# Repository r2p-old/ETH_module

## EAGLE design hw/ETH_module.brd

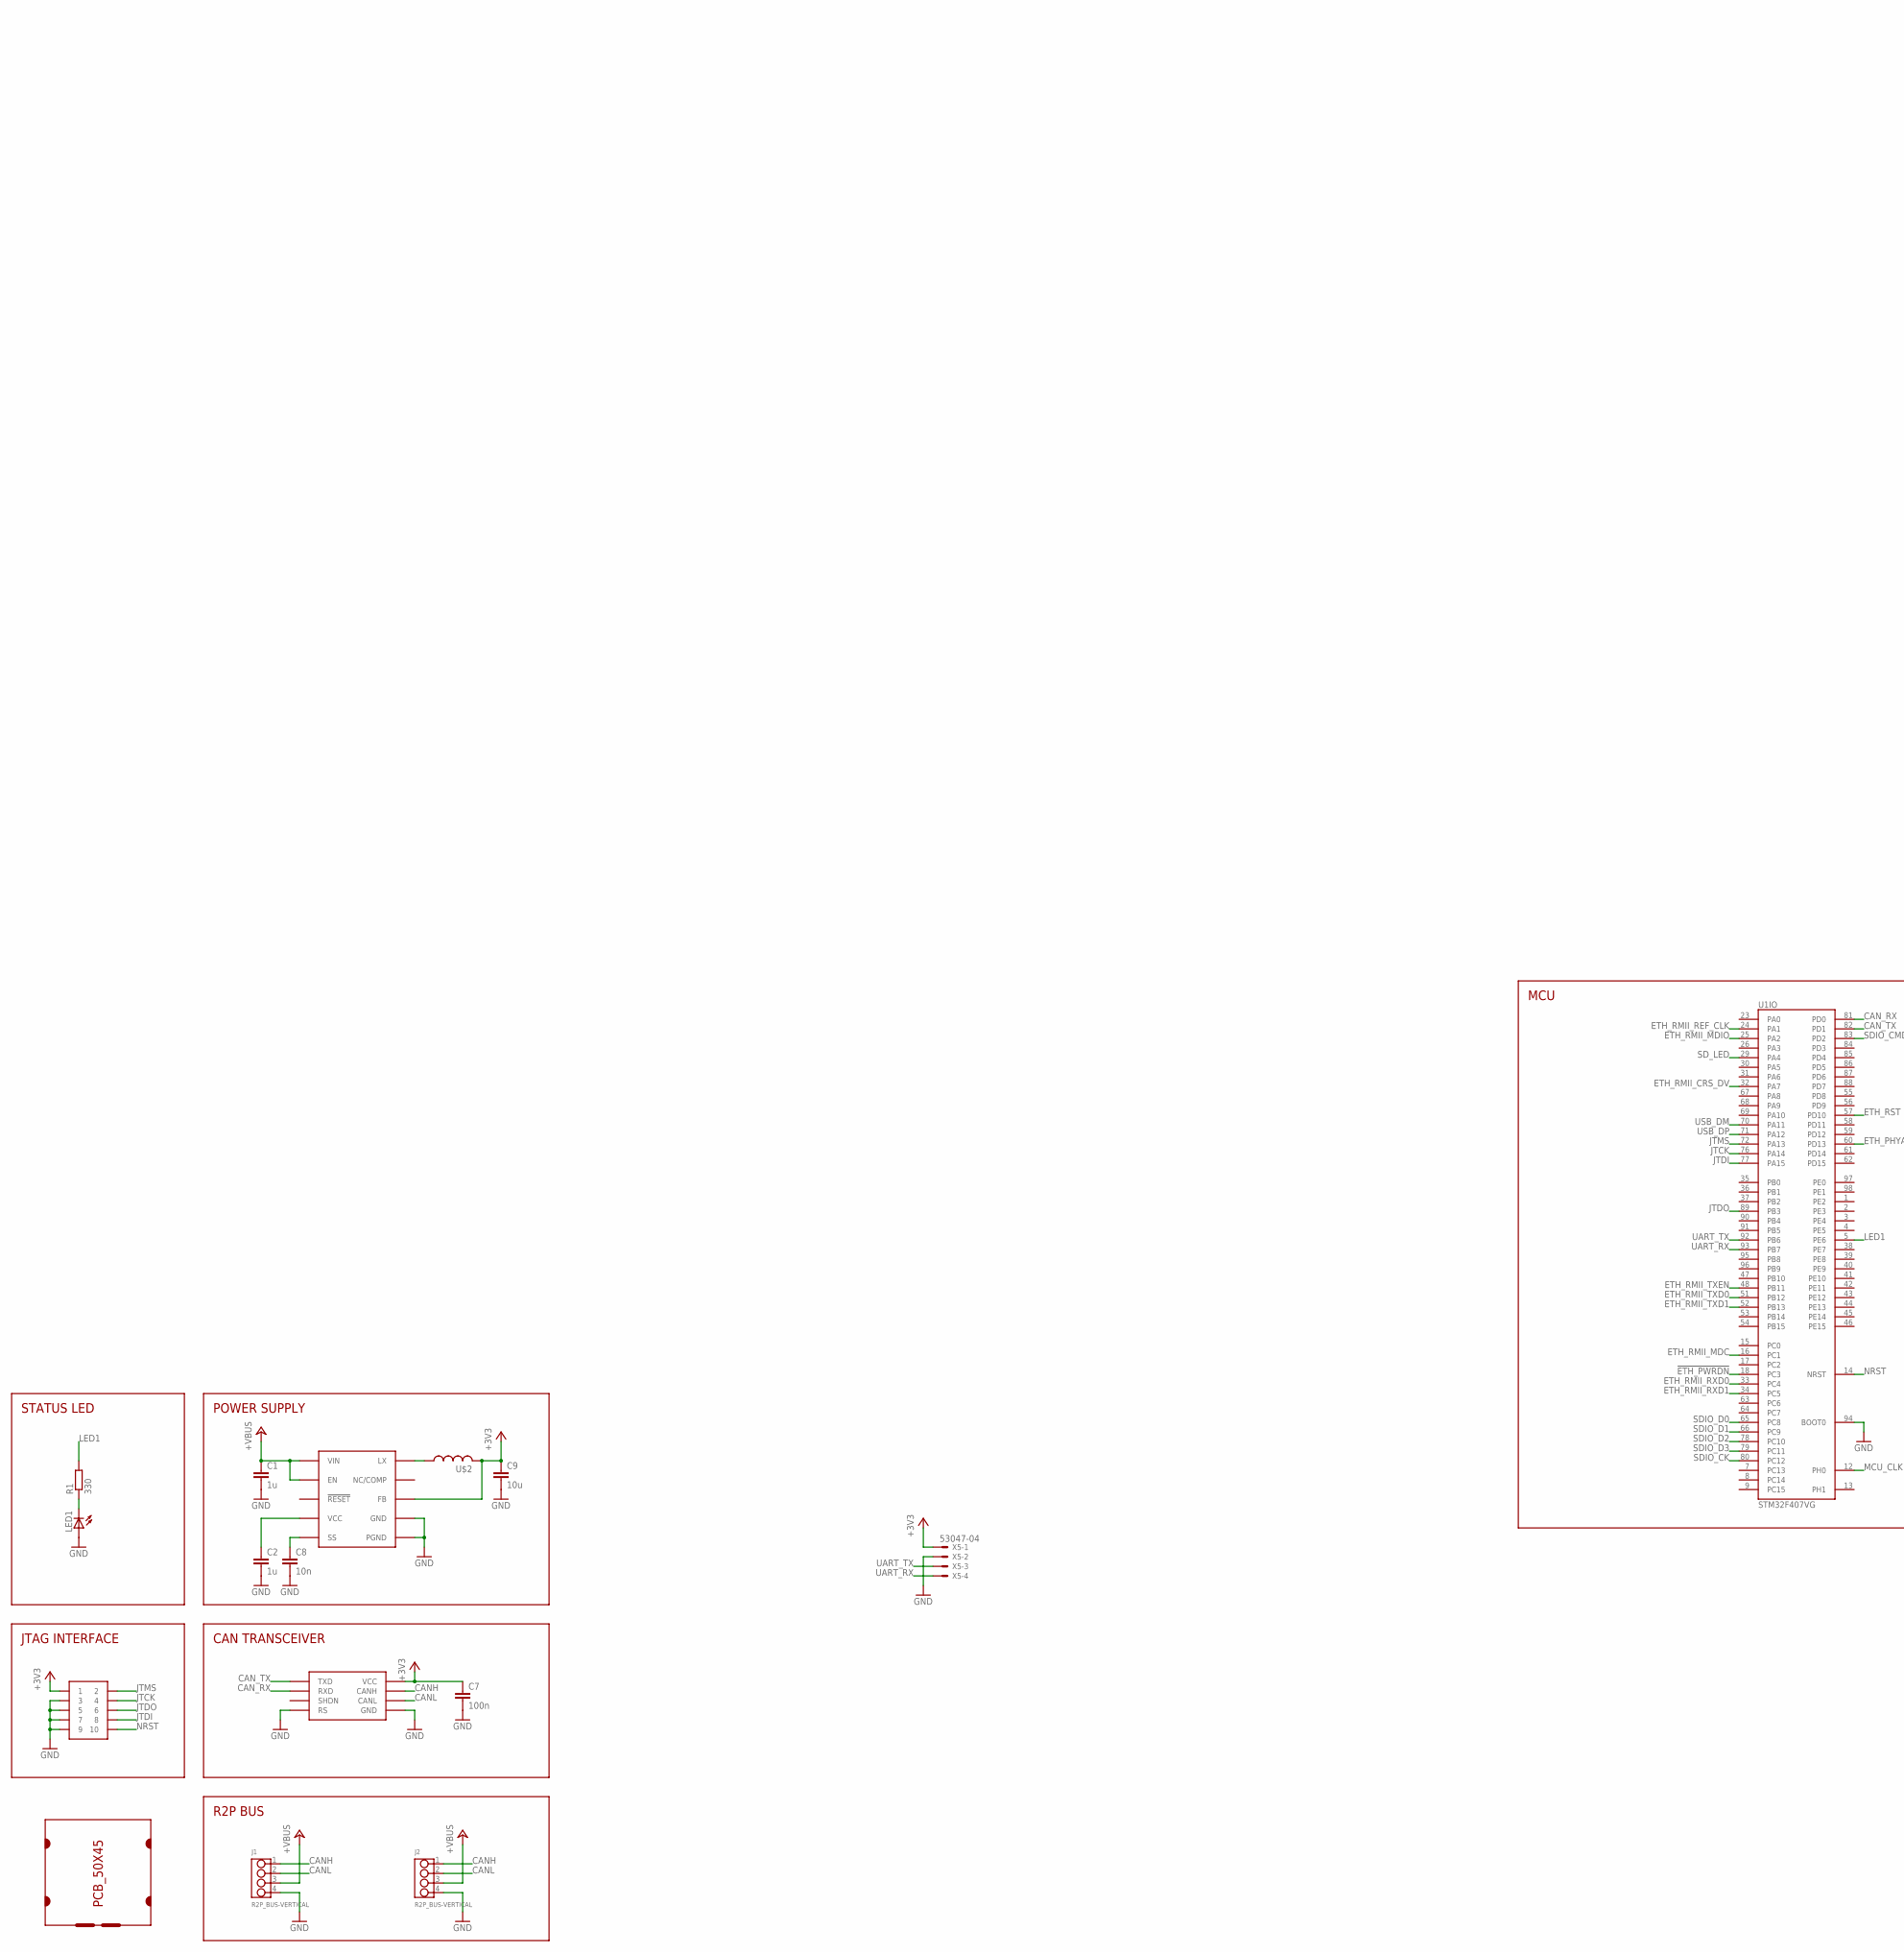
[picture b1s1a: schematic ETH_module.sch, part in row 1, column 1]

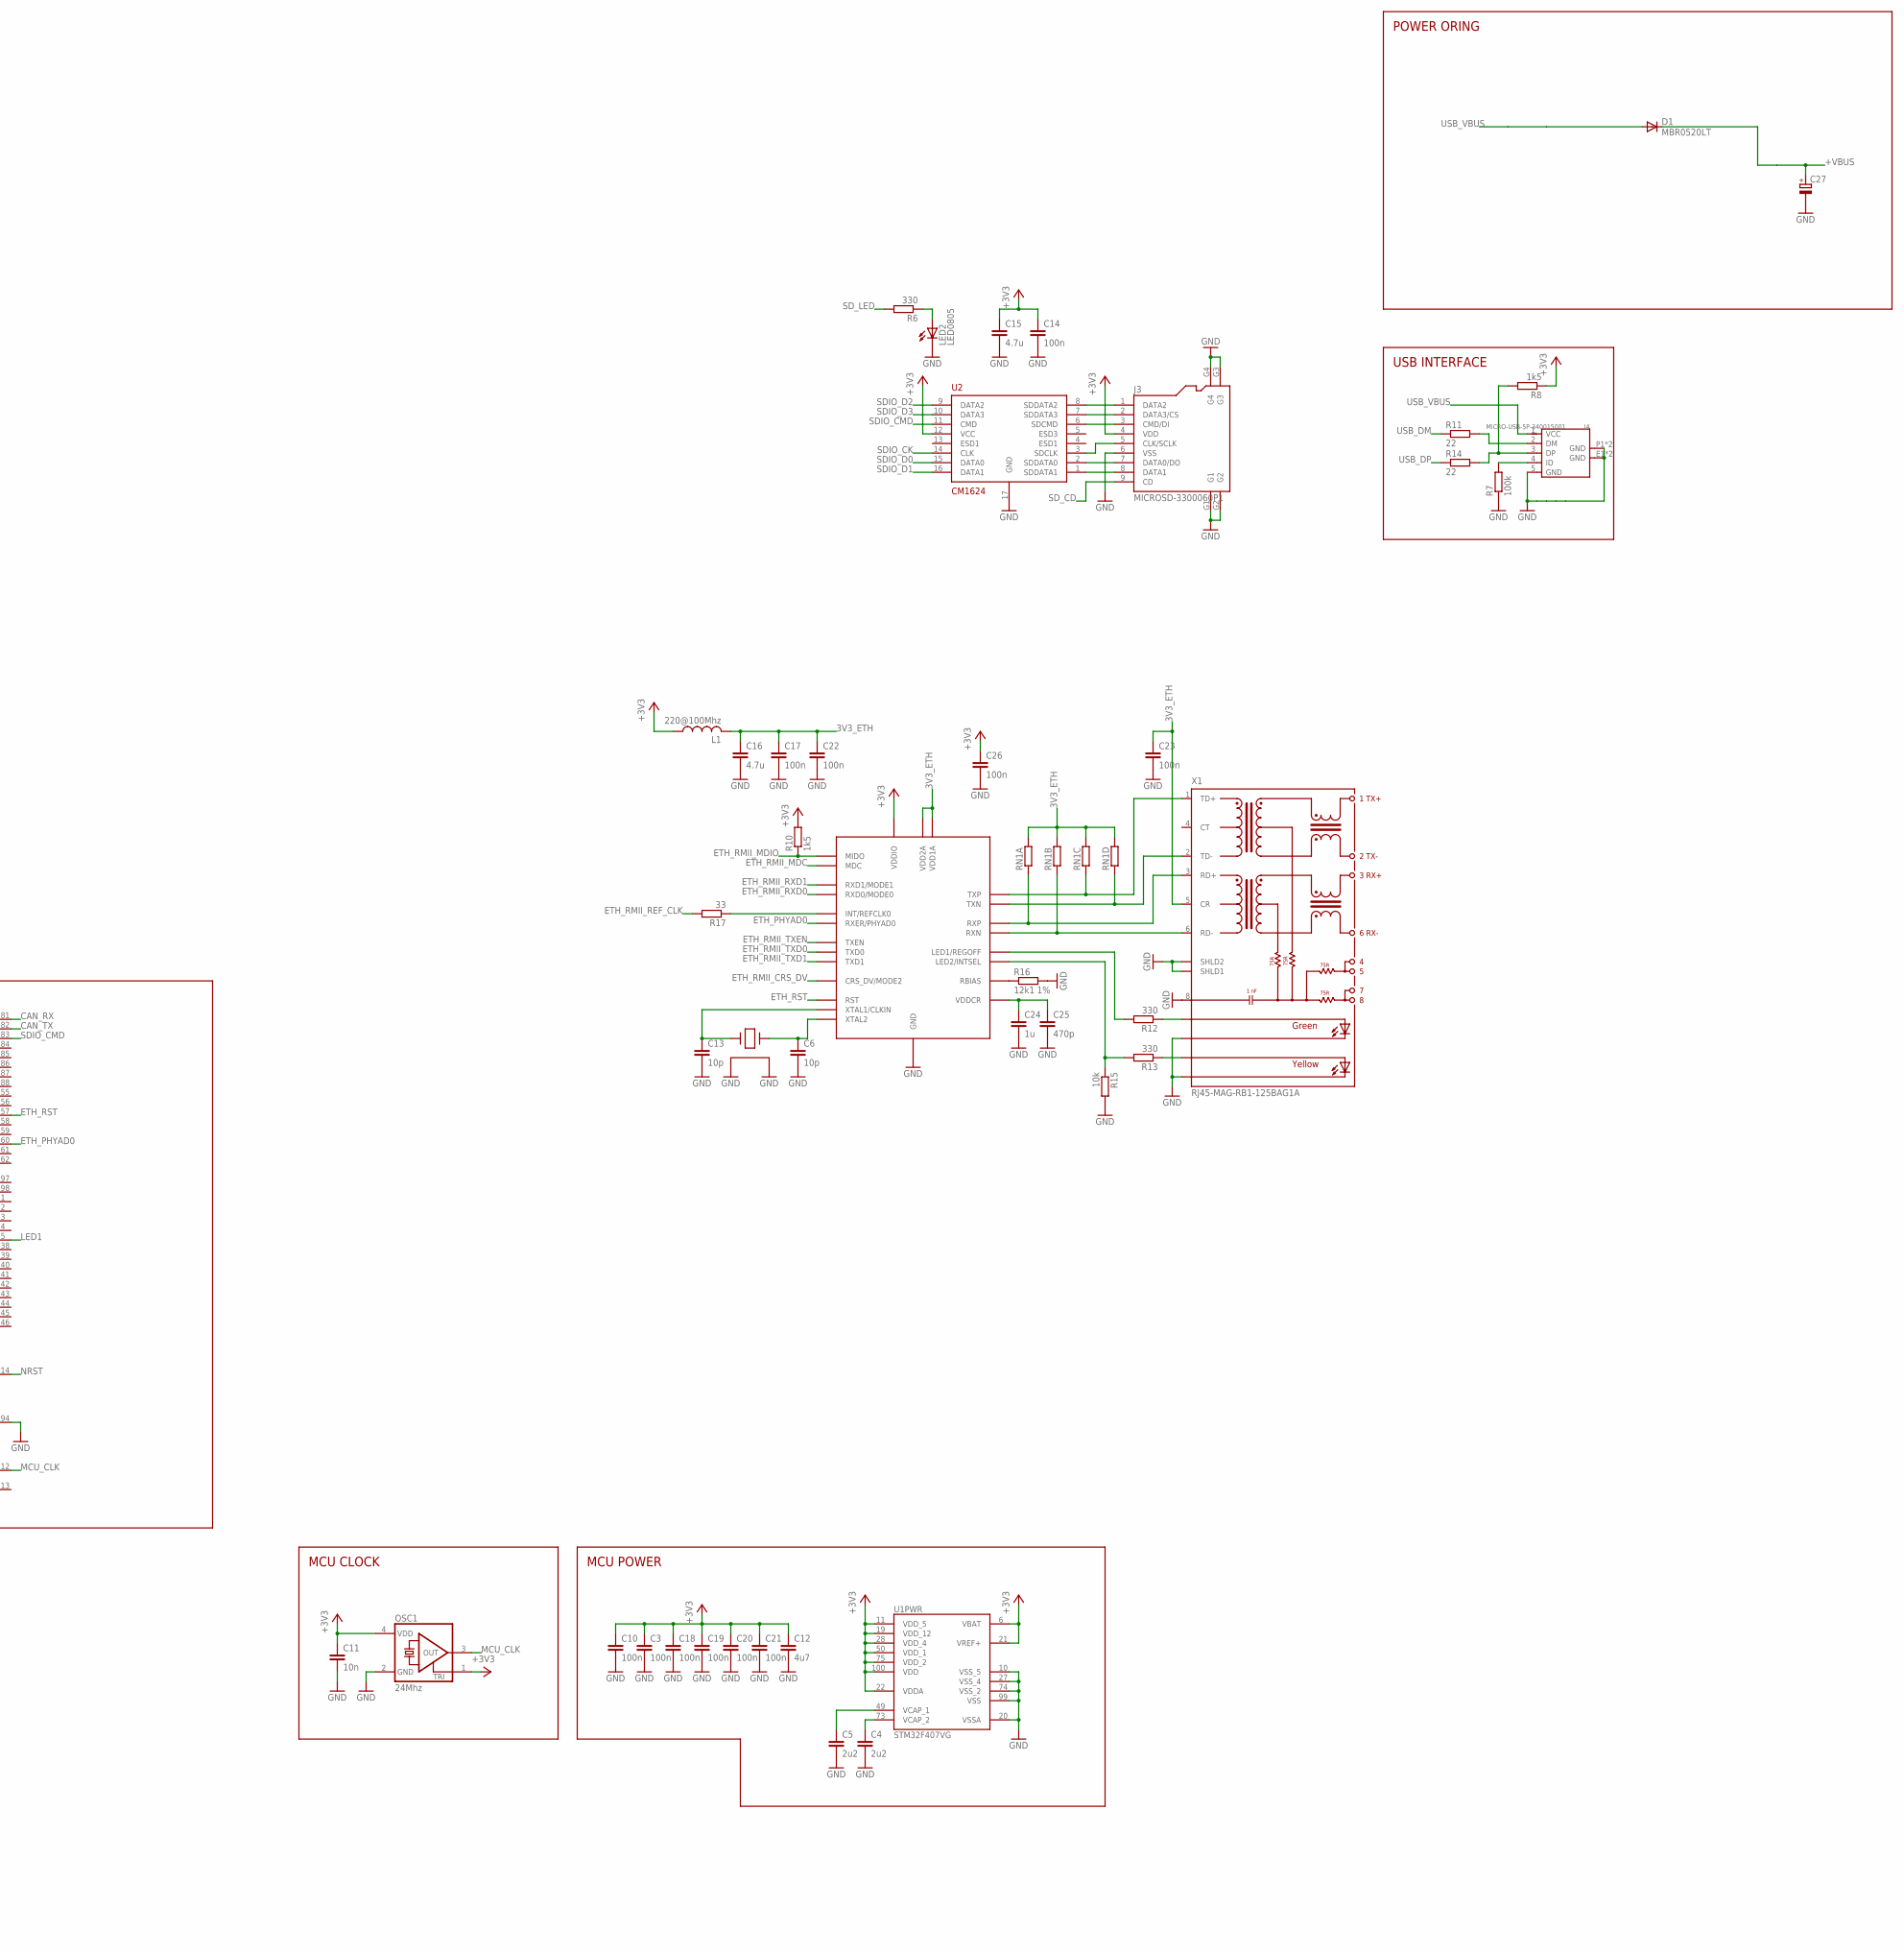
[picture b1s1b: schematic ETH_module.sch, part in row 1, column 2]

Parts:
C1: 1u; C1206
C2, C24: 1u; C0603
C3, C7, C10, C14, C17, C18, C19, C20, C21, C22, C23, C26: 100n; C0603
C4, C5: 2u2; C0603
C6, C13: 10p; C0603
C8, C11: 10n; C0603
C9: 10u; C0805
C12: 4u7; C0805
C15, C16: 4.7u; C0805
C25: 470p; C0603
C27: CPOL-EUB/3528-21R; B/3528-21R
D1: MBR0520LT; SOD123
J1, J2: R2P_BUS-VERTICAL; OPL-EAGLE-LIBRARY_4P-2.0
J3: MICROSD-3300060P1; 9P-SMD-W-RING
J4: MICRO-USB-5P-340015001; B-SMD-5P
L1: 220@100Mhz; L0603
LED1, LED2: LED0805; CHIPLED_0805
OSC1: 24Mhz; XTAL_2.5X2
R1, R6, R12, R13: 330; R0603
R7: 100k; R0603
R8, R10: 1k5; R0603
R11, R14: 22; R0603
R15: 10k; R0603
R16: 12k1 1%; R0603
R17: 33; R0603
RN1: RNETWORK_4-1206; RNET4_1206
SOT1: MAX3051EKA; SOT23-8L
U1: STM32F407VG; LQFP100
U2: CM1624; UDFN16
U$1: PCB_50X45; 50X45
U$2: LPS4018; COILCRAFT_LPS4018
U$3: MAX17501; TDFN-10
U$4: JTAG-TH; SAMTEC_FTSH-105-TH
U$5: LAN8720A; QFN24
U$6: XTAL-2.5X2; XTAL_2.5X2
X1: RJ45-MAG-RB1-125BAG1A; WIZNET_RB1-125BAG1A
X5: 53047-04

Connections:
3V3_ETH: C16.1, C17.1, C22.1, C23.1, L1.2, RN1.5 (2), RN1.6 (2), RN1.7 (2), RN1.8 (2), U$5.P$1 (VDD2A), U$5.P$19 (VDD1A), X1.5 (CR)
!ETH_PWRDN: U1.18 (PC3)
+3V3: C3.1, C7.1, C9.1, C10.1, C11.1, C12.1, C14.1, C15.1, C18.1, C19.1, C20.1, C21.1, C26.1, J3.4 (VDD), L1.1, OSC1.1 (TRI), OSC1.4 (VDD), R8.1, R10.2, SOT1.3 (VCC), U1.6 (VBAT), U1.11 (VDD_5), U1.19 (VDD_12), U1.21 (VREF+), U1.22 (VDDA), U1.28 (VDD_4), U1.50 (VDD_1), U1.75 (VDD_2), U1.100 (VDD), U2.12 (VCC), U$2.P$2 (2), U$3.P$5 (FB), U$4.1, U$5.P$9 (VDDIO), X5.1
+VBUS: C1.1, C27.+, D1.C, J1.3, J2.3, U$3.P$2 (VIN), U$3.P$3 (EN)
CANH: J1.1, J2.1, SOT1.7 (CANH)
CANL: J1.2, J2.2, SOT1.6 (CANL)
CAN_RX: SOT1.4 (RXD), U1.81 (PD0)
CAN_TX: SOT1.1 (TXD), U1.82 (PD1)
ETH_PHYAD0: U1.60 (PD13), U$5.P$10 (RXER/PHYAD0)
ETH_RMII_CRS_DV: U1.32 (PA7), U$5.P$11 (CRS_DV/MODE2)
ETH_RMII_MDC: U1.16 (PC1), U$5.P$13 (MDC)
ETH_RMII_MDIO: R10.1, U1.25 (PA2), U$5.P$12 (MIDO)
ETH_RMII_REF_CLK: R17.2, U1.24 (PA1)
ETH_RMII_RXD0: U1.33 (PC4), U$5.P$8 (RXD0/MODE0)
ETH_RMII_RXD1: U1.34 (PC5), U$5.P$7 (RXD1/MODE1)
ETH_RMII_TXD0: U1.51 (PB12), U$5.P$17 (TXD0)
ETH_RMII_TXD1: U1.52 (PB13), U$5.P$18 (TXD1)
ETH_RMII_TXEN: U1.48 (PB11), U$5.P$16 (TXEN)
ETH_RST: U1.57 (PD10), U$5.P$15 (RST)
GND: C1.2, C2.2, C3.2, C4.2, C5.2, C6.2, C7.2, C8.2, C9.2, C10.2, C11.2, C12.2, C13.2, C14.2, C15.2, C16.2, C17.2, C18.2, C19.2, C20.2, C21.2, C22.2, C23.2, C24.2, C25.2, C26.2, C27.-, J1.4, J2.4, J3.6 (VSS), J3.G1, J3.G2, J3.G3, J3.G4, J4.5 (GND), J4.E1 (GND), J4.E2 (GND), J4.P1 (GND), J4.P2 (GND), LED1.A, LED2.C, OSC1.2 (GND), R7.1, R15.2, R16.2, SOT1.2 (GND), SOT1.8 (RS), U1.10 (VSS_5), U1.20 (VSSA), U1.27 (VSS_4), U1.74 (VSS_2), U1.94 (BOOT0), U1.99 (VSS), U2.17 (GND), U$3.P$1 (PGND), U$3.P$9 (GND), U$3.P$11 (PGND), U$4.3, U$4.5, U$4.7, U$4.9, U$5.P$25 (GND), U$6.2, U$6.4, X1.8, X1.9 (SHLD1), X1.10 (SHLD2), X1.L2 (YK), X1.L4 (GK), X5.2
JTCK: U1.76 (PA14), U$4.4
JTDI: U1.77 (PA15), U$4.8
JTDO: U1.89 (PB3), U$4.6
JTMS: U1.72 (PA13), U$4.2
LED1: R1.2, U1.5 (PE6)
MCU_CLK: OSC1.3 (OUT), U1.12 (PH0)
unnamed: U$2.P$1 (1), U$3.P$10 (LX)
unnamed: LED1.C, R1.1
unnamed: LED2.A, R6.1
unnamed: C2.1, U$3.P$4 (VCC)
unnamed: C8.1, U$3.P$6 (SS)
unnamed: J4.2 (DM), R11.2
unnamed: J4.4 (ID), R7.2
unnamed: J3.1 (DATA2), U2.8 (SDDATA2)
unnamed: J3.2 (DATA3/CS), U2.7 (SDDATA3)
unnamed: J3.3 (CMD/DI), U2.6 (SDCMD)
unnamed: J3.5 (CLK/SCLK), U2.3 (SDCLK)
unnamed: R17.1, U$5.P$14 (INT/REFCLK0)
unnamed: J3.7 (DATA0/DO), U2.2 (SDDATA0)
unnamed: J3.8 (DATA1), U2.1 (SDDATA1)
unnamed: C13.1, U$5.P$5 (XTAL1/CLKIN), U$6.1
unnamed: C6.1, U$5.P$4 (XTAL2), U$6.3
unnamed: R12.2, U$5.P$3 (LED1/REGOFF)
unnamed: R12.1, X1.L3 (GA)
unnamed: R13.1, X1.L1 (YA)
unnamed: R13.2, R15.1, U$5.P$2 (LED2/INTSEL)
unnamed: C24.1, C25.1, U$5.P$6 (VDDCR)
unnamed: R16.1, U$5.P$24 (RBIAS)
unnamed: J4.3 (DP), R8.2, R14.2
NRST: U1.14 (NRST), U$4.10
RX_N: RN1.2 (1), U$5.P$22 (RXN), X1.6 (RD-)
RX_P: RN1.1, U$5.P$23 (RXP), X1.3 (RD+)
SDIO_CK: U1.80 (PC12), U2.14 (CLK)
SDIO_CMD: U1.83 (PD2), U2.11 (CMD)
SDIO_D0: U1.65 (PC8), U2.15 (DATA0)
SDIO_D1: U1.66 (PC9), U2.16 (DATA1)
SDIO_D2: U1.78 (PC10), U2.9 (DATA2)
SDIO_D3: U1.79 (PC11), U2.10 (DATA3)
SD_CD: J3.9 (CD)
SD_LED: R6.2, U1.29 (PA4)
TX_N: RN1.4 (1), U$5.P$20 (TXN), X1.2 (TD-)
TX_P: RN1.3 (1), U$5.P$21 (TXP), X1.1 (TD+)
UART_RX: U1.93 (PB7), X5.4
UART_TX: U1.92 (PB6), X5.3
USB_DM: R11.1, U1.70 (PA11)
USB_DP: R14.1, U1.71 (PA12)
USB_VBUS: D1.A, J4.1 (VCC)
VCAP_1: C5.1, U1.49 (VCAP_1)
VCAP_2: C4.1, U1.73 (VCAP_2)

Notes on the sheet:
STATUS LED
JTAG INTERFACE
POWER SUPPLY
CAN TRANSCEIVER
R2P BUS
MCU
MCU POWER
MCU CLOCK
USB INTERFACE
POWER ORING

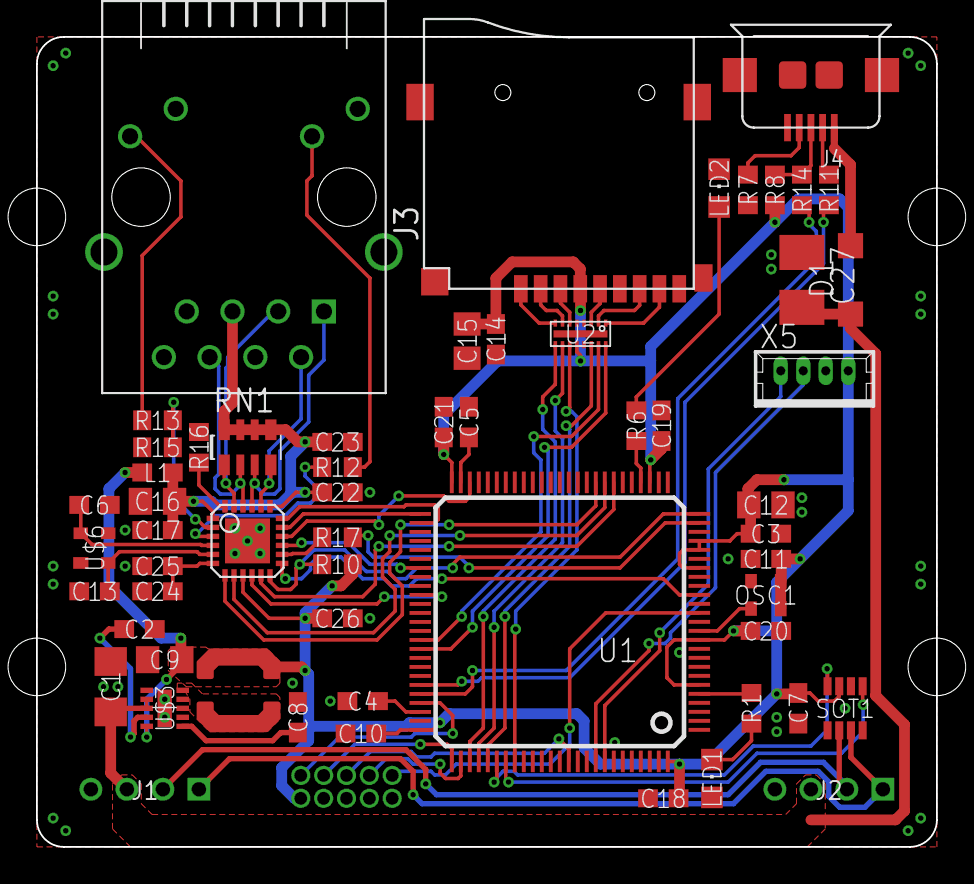
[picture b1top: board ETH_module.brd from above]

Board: 2 copper layers, 50.0 x 45.0 mm, 60 parts (0 on the bottom side), 67 nets.

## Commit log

2015-02-12 Working on PHY layout
2015-02-13 Layout complete
2015-02-13 Added makefile
2015-02-19 Fixed directory creation
2015-02-19 Fixed silkscreen
